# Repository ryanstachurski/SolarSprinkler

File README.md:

# SolarSprinkler
Solar-powered rain-barrel pumping irrigation for your garden.  Runs on the low-cost Arduino-based ESP8266.

## Files
- *SolarSprinkler.ino* - Arduino code for ESP8266 
  - Implement clock time, pump start time, and pump cycles per day
- *SolarSprinkler.sch* - Eagle schematic file
- *SolarSprinkler.brd* - Eagle board file
- *SolarSprinklerLogo.bmp* - Bitmap logo

## Project Home
http://stachurski.us/solar-sprinkler/

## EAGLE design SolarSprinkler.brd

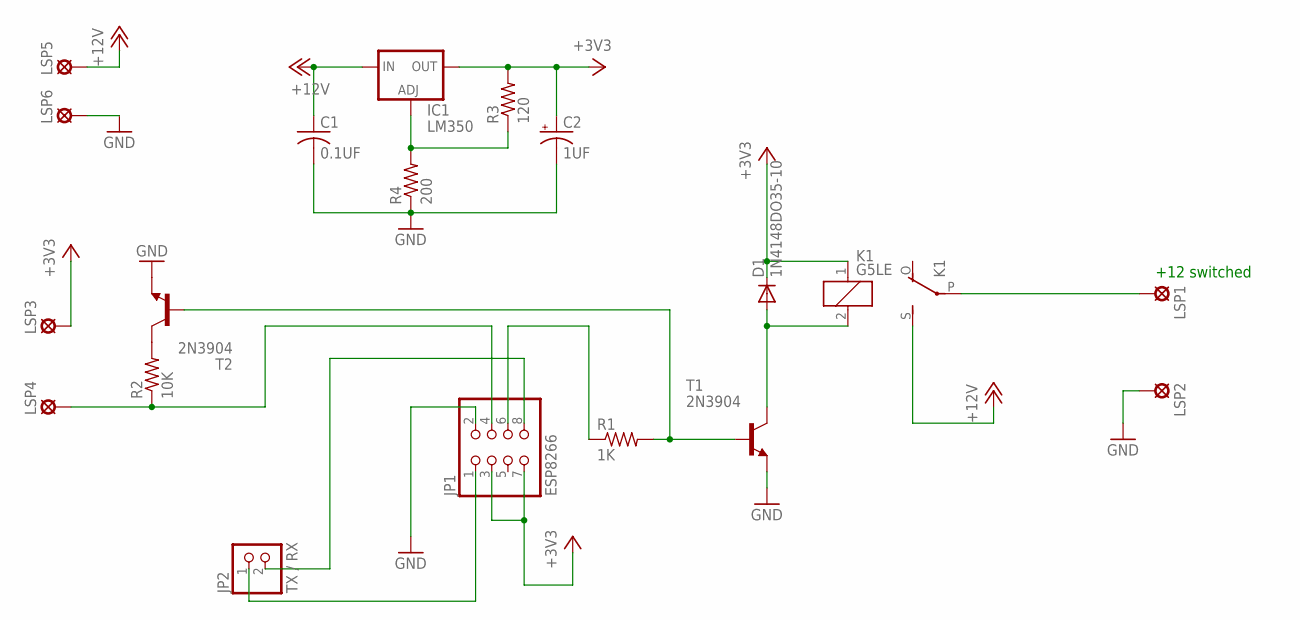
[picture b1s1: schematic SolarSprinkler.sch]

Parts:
C1: 0.1UF; C025-030X050
C2: 1UF; E2,5-5
D1: 1N4148DO35-10; DO35-10
IC1: LM350; 317TL
JP1: ESP8266; 2X04
JP2: TX / RX; 1X02
K1: G5LE
LSP1, LSP2, LSP3, LSP4, LSP5, LSP6: SE14
R1: 1K; 0309/12
R2: 10K; 0309/12
R3: 120; 0309/12
R4: 200; 0309/12
T1, T2: 2N3904; TO92

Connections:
+3V3: C2.+, D1.C, IC1.2 (OUT), JP1.3, JP1.7, K1.1, LSP3.MP, R3.2
+12V: C1.1, IC1.3 (IN), K1.S, LSP5.MP
GND: C1.2, C2.-, JP1.2, LSP2.MP, LSP6.MP, R4.1, T1.3 (E), T2.3 (E)
unnamed: JP1.6, R1.1
unnamed: R1.2, T1.2 (B), T2.2 (B)
unnamed: D1.A, K1.2, T1.1 (C)
unnamed: R2.2, T2.1 (C)
unnamed: K1.P, LSP1.MP
unnamed: JP1.4, LSP4.MP, R2.1
unnamed: IC1.1 (ADJ), R3.1, R4.2
unnamed: JP1.8, JP2.2
unnamed: JP1.1, JP2.1

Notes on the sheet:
+12 switched

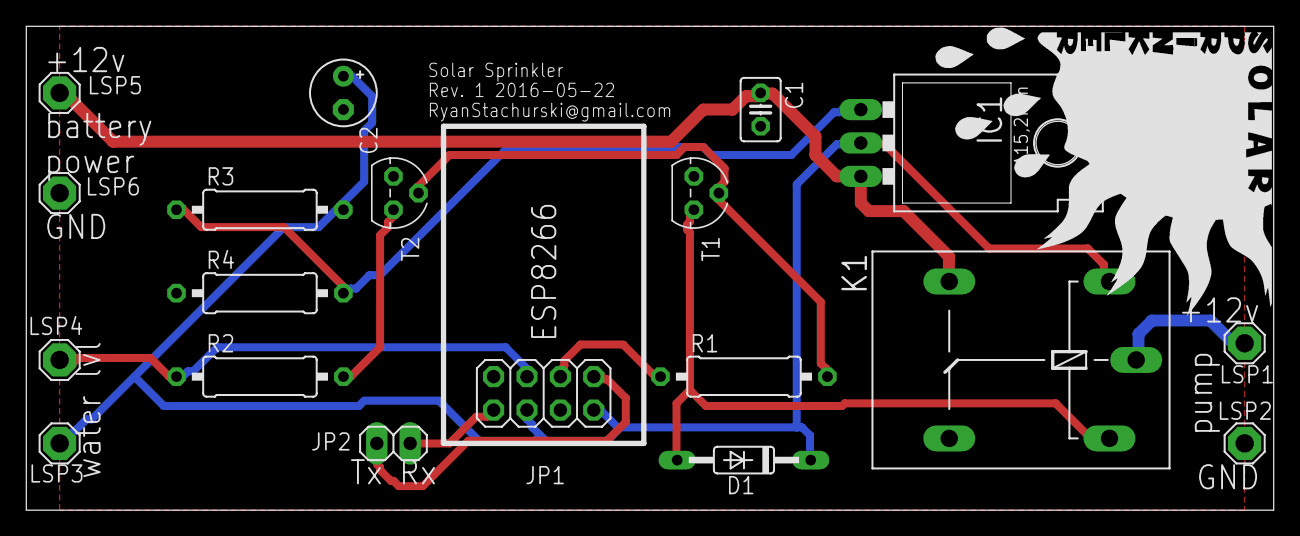
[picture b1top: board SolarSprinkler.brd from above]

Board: 2 copper layers, 94.9 x 36.8 mm, 19 parts (0 on the bottom side), 12 nets.

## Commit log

2016-07-09 Create SolarSprinkler
2016-07-09 Update README.md
    Update file list
2016-08-05 Create solarsprinklerlogo.txt
    SolarSprinkler logo converted to base64
